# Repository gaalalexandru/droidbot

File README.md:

# droidbot
Tiva TM4C123GH6PM powered 2 wheel robot

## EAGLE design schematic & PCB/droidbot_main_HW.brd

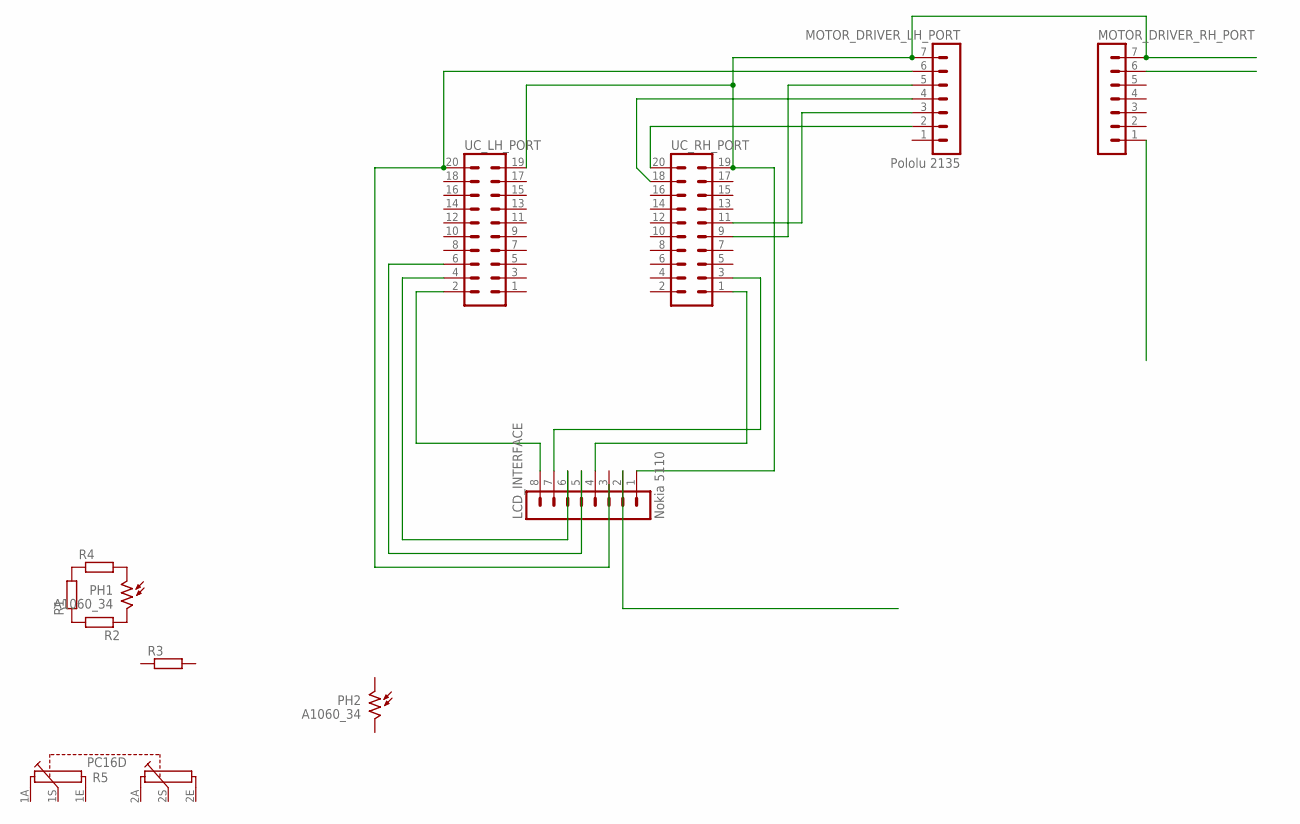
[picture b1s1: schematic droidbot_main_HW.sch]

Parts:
LCD_INTERFACE: Nokia 5110; MA08-1
MOTOR_DRIVER_LH_PORT: Pololu 2135; MA07-1
MOTOR_DRIVER_RH_PORT: MA07-1
PH1, PH2: A1060_34; T0-46-A10XX
R1, R2, R3, R4: R0204/7; 0204/7
R5: PC16D
UC_LH_PORT: MA10-2
UC_RH_PORT: MA10-2

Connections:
unnamed: LCD_INTERFACE.8, UC_LH_PORT.2
unnamed: LCD_INTERFACE.7, UC_RH_PORT.3
unnamed: LCD_INTERFACE.6, UC_LH_PORT.4
unnamed: LCD_INTERFACE.5, UC_LH_PORT.6
unnamed: LCD_INTERFACE.4, UC_RH_PORT.1
unnamed: MOTOR_DRIVER_LH_PORT.5, UC_RH_PORT.9
unnamed: MOTOR_DRIVER_LH_PORT.6, UC_LH_PORT.20
unnamed: LCD_INTERFACE.1, MOTOR_DRIVER_LH_PORT.7, MOTOR_DRIVER_RH_PORT.7, UC_LH_PORT.19, UC_RH_PORT.19
unnamed: MOTOR_DRIVER_LH_PORT.4, UC_RH_PORT.18
unnamed: MOTOR_DRIVER_LH_PORT.2, UC_RH_PORT.20
unnamed: MOTOR_DRIVER_LH_PORT.3, UC_RH_PORT.11
unnamed: R1.1, R2.2
unnamed: R1.2, R4.1
unnamed: PH1.2, R2.1
unnamed: PH1.1, R4.2

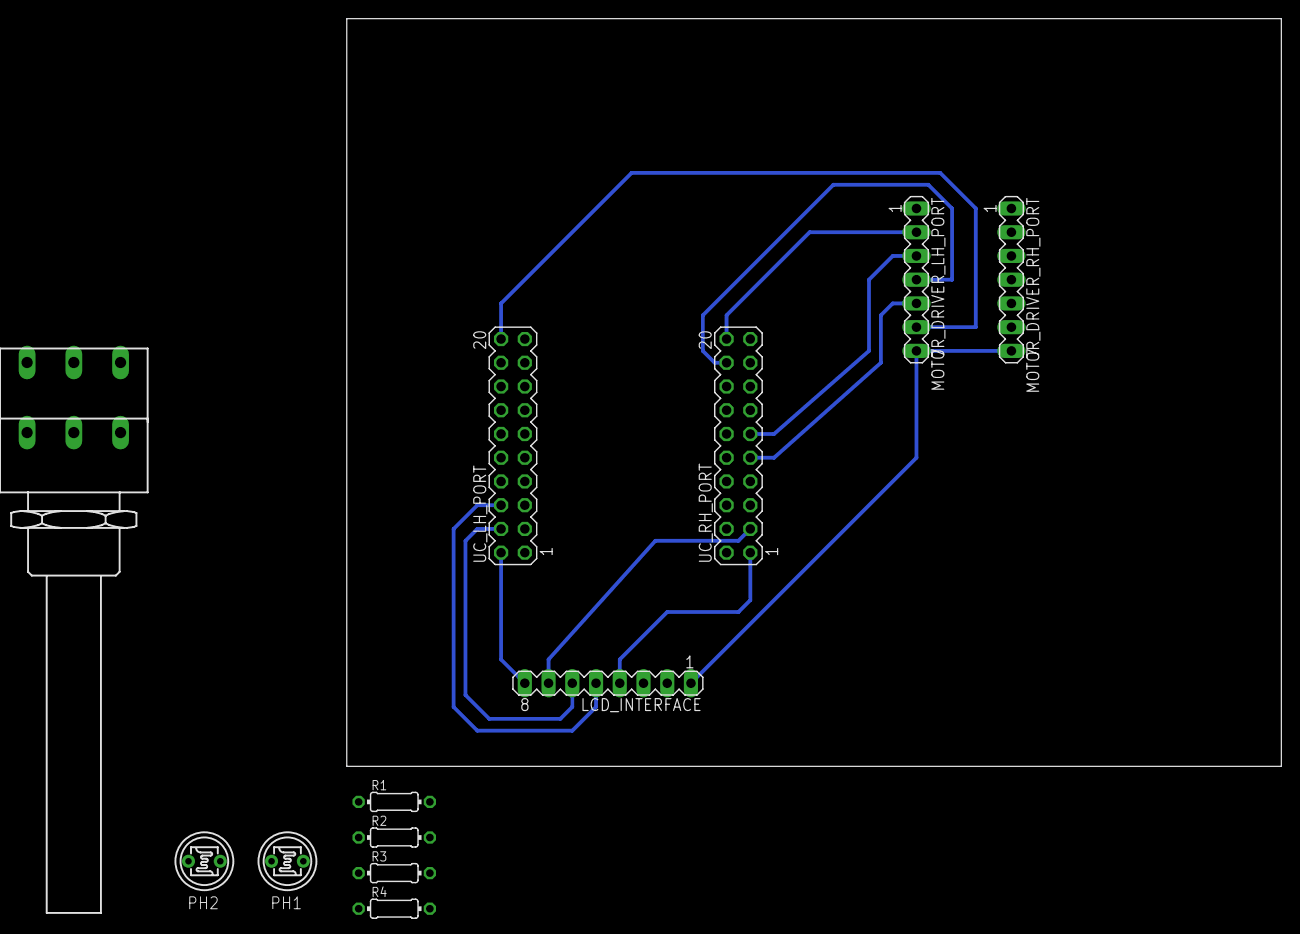
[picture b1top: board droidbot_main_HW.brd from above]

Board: 2 copper layers, 100.0 x 80.0 mm, 12 parts (0 on the bottom side), 15 nets.

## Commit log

2016-01-06 test commpit
    just to test out services
2016-01-06 initial sync
    first syncronization of the source code
2016-01-06 sync complete
    I think it works :)
2016-01-06 added dc motor driver datasheed
2016-01-06 compiled and mod comments
    1) compiled to check for errors
    2) reduced tab between code and comments in pwm handler C file
2016-01-06 closed project
2016-01-07 50ms timer 0a added
2016-01-07 added ISR for 50ms timer and disabled generation of list and output files
2016-01-07 created 50 ms cyclic function container
2016-01-07 updated to do list
2016-01-11 updated pin layout tab
2016-01-11 chosen motor & driver HW, updated documentation
2016-01-22 small changes
2016-01-22 can files added
2016-01-24 Started developing CAN init function
2016-01-24 nothing
2016-01-27 initial schematic in eagle
2016-01-27 updated pin layout
2016-01-27 work on schematic and pcb
2016-02-02 added alternative dc motor supplier
2016-02-03 minor changes
2016-02-03 updated documentation
2016-02-03 started creating function
2016-02-07 some changes
2016-02-16 Light sensor design
2016-02-16 added back file
2016-02-18 motor mode select
2016-02-25 some documentation added
2016-04-14 modas
2016-04-15 temp sensor and light sensor 1
2016-04-24 adc light sensor input updates
2016-04-24 LS algoritm
2016-05-11 234234
2016-05-12 documentation updates
2016-06-21 documentation update
2016-06-21 adc updates
    mx sensor moved from ss3 to ss0
2016-06-21 adc updates 2
2016-06-28 overal updates
2016-07-03 corections
2016-07-05 updated system startup routine
2016-07-05 none
2016-07-07 I2C development started, GPIO motor direction selct updated
2016-07-07 I2C minor updates and documentation
2016-07-08 I2C Service development - WIP
2016-07-10 I2C and Accelerometer development
2016-07-10 i2c service development
2016-07-10 i2c development
2016-07-14 shift reg documentation added
2016-07-14 SSI and Shift register handler development
2016-07-20 I2C Read function development
2016-08-24 i2c example added
2016-08-25 UART Debugging added
    3rd party driver
2016-09-13 work on i2c
2017-01-03 started inplementing ssOS to Droidbot SW
2017-01-03 inplementing ssOS to Droidbot
2017-01-04 finished inplementing ssOS on Droidbot
2017-01-05 system clock set removed
2017-01-05 updated xls file
2017-02-21 added ssOS 1.2, LCD not working
2017-04-08 minor fix
2018-05-28 update gitignore
